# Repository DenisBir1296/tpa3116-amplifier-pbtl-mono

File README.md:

tpa3116 PBTL mono amplifier board

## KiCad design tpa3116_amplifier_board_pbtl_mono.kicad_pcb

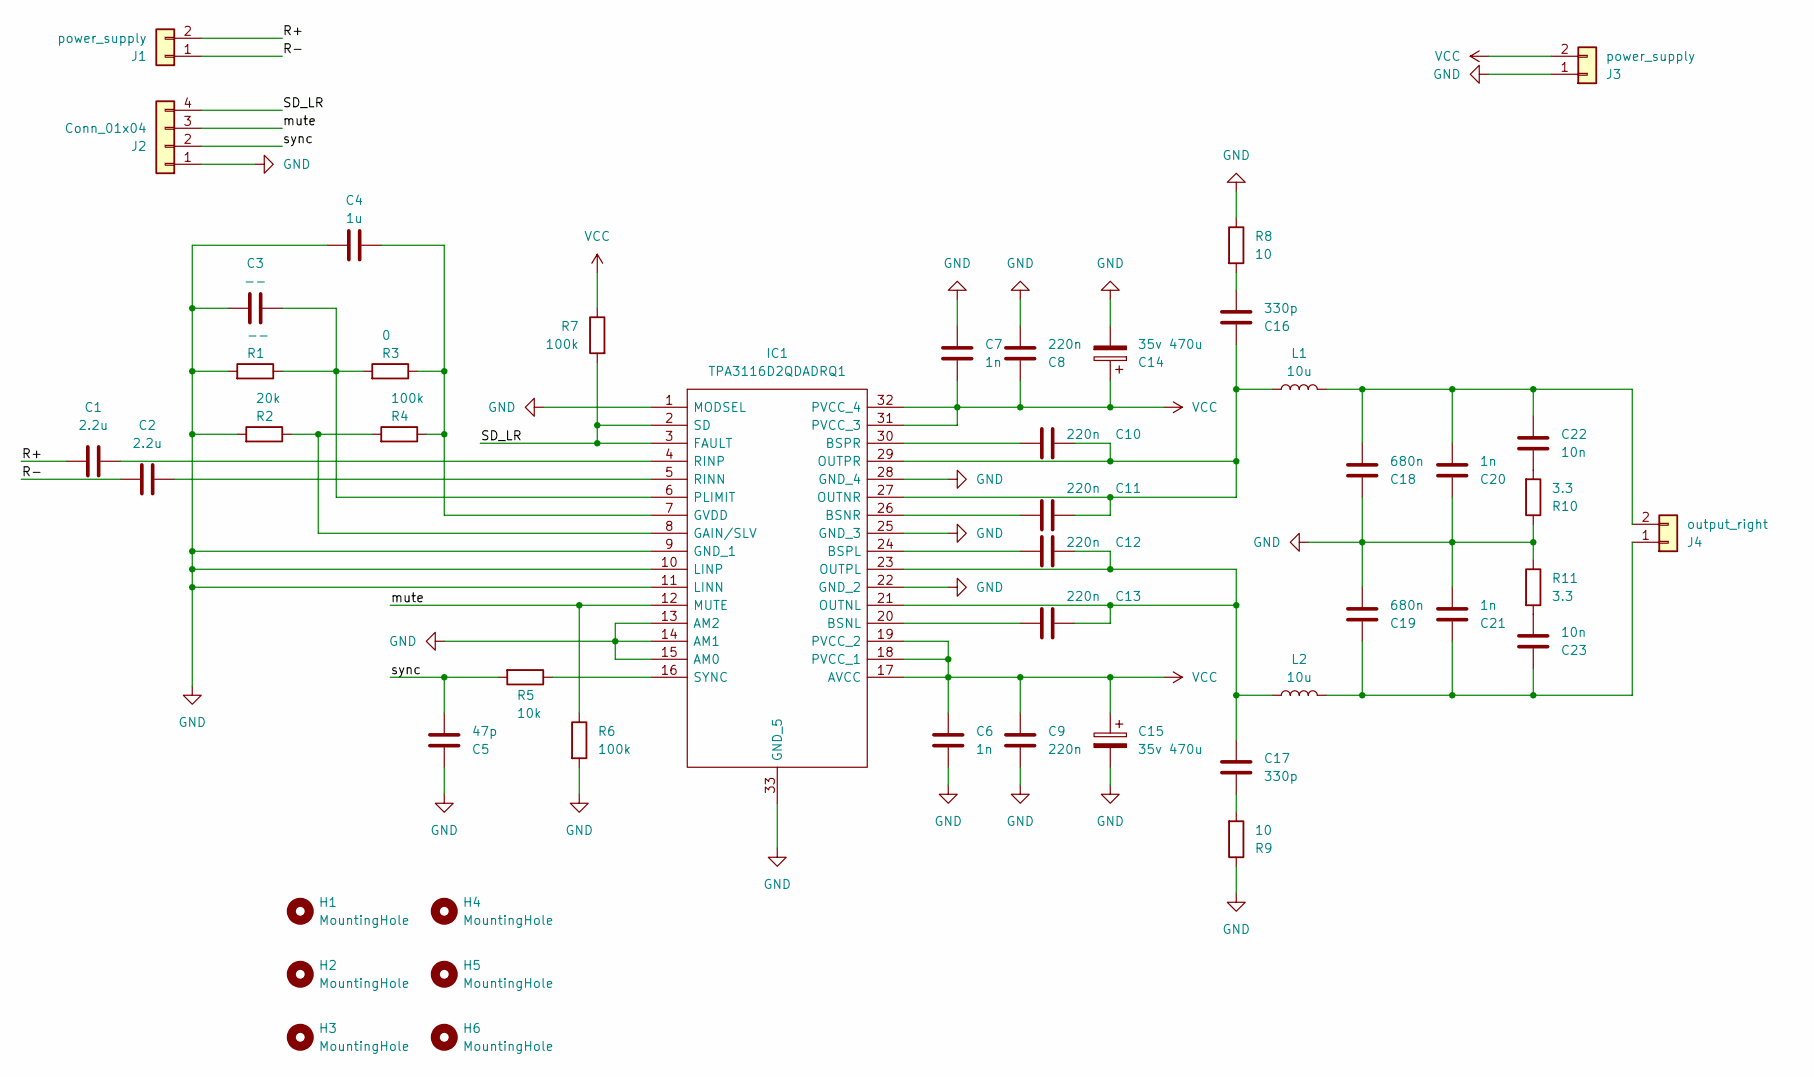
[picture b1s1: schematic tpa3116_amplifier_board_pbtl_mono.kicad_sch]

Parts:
C1, C2: 2.2u; C_0805_2012Metric
C3: --; C_0805_2012Metric
C4: 1u; C_0805_2012Metric
C5: 47p; C_0603_1608Metric
C6, C7, C20, C21: 1n; C_0603_1608Metric
C8, C9, C10, C11, C12, C13: 220n; C_0603_1608Metric
C14, C15: 35v 470u; CP_Radial_D10.0mm_P5.00mm
C16, C17: 330p; C_0603_1608Metric
C18, C19: 680n; C_1812_4532Metric
C22, C23: 10n; C_0603_1608Metric
H1, H2, H3, H4, H5, H6: MountingHole; MountingHole_3.2mm_M3_DIN965_Pad
IC1: TPA3116D2QDADRQ1; SOP65P810X120-33N; Manufacturer_Part_Number TPA3116D2QDADRQ1; Mouser Part Number 595-TPA3116D2QDADRQ1
J1: power_supply; JST_PH_B2B-PH-K_1x02_P2.00mm_Vertical
J2: Conn_01x04; JST_PH_B4B-PH-K_1x04_P2.00mm_Vertical
J3: power_supply; JST_VH_B2P-VH-B_1x02_P3.96mm_Vertical
J4: output_right; JST_VH_B2P-VH-B_1x02_P3.96mm_Vertical
L1, L2: 10u; L_12x12mm_H8mm
R1: --; R_0603_1608Metric
R2: 20k; R_0603_1608Metric
R3: 0; R_0603_1608Metric
R4, R6, R7: 100k; R_0603_1608Metric
R5: 10k; R_0603_1608Metric
R8, R9: 10; R_0805_2012Metric
R10, R11: 3.3; R_0603_1608Metric

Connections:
/R+: C1.1, J1.2
/R-: C2.1, J1.1
/SD_LR: IC1.2 (SD), IC1.3 (FAULT), J2.4, R7.2
/mute: IC1.12 (MUTE), J2.3, R6.1
/sync: C5.2, J2.2, R5.2
GND: C3.1, C4.1, C5.1, C6.2, C7.1, C8.2, C9.2, C14.2, C15.2, C18.1, C19.2, C20.1, C21.2, IC1.1 (MODSEL), IC1.9 (GND_1), IC1.10 (LINP), IC1.11 (LINN), IC1.13 (AM2), IC1.14 (AM1), IC1.15 (AM0), IC1.22 (GND_2), IC1.25 (GND_3), IC1.28 (GND_4), IC1.33 (GND_5), J2.1, J3.1, R1.2, R2.2, R6.2, R8.1, R9.1, R10.1, R11.1
unnamed: C16.2, R8.2
unnamed: C17.2, R9.2
unnamed: C22.2, R10.2
unnamed: C23.2, R11.2
unnamed: C13.2, IC1.20 (BSNL)
unnamed: C11.2, IC1.26 (BSNR)
unnamed: C12.2, IC1.24 (BSPL)
unnamed: C10.2, IC1.30 (BSPR)
unnamed: IC1.8 (GAIN/SLV), R2.1, R4.2
unnamed: C4.2, IC1.7 (GVDD), R3.1, R4.1
unnamed: C12.1, C13.1, C17.1, IC1.21 (OUTNL), IC1.23 (OUTPL), L2.1
unnamed: C10.1, C11.1, C16.1, IC1.27 (OUTNR), IC1.29 (OUTPR), L1.1
unnamed: C3.2, IC1.6 (PLIMIT), R1.1, R3.2
unnamed: C2.2, IC1.5 (RINN)
unnamed: C1.2, IC1.4 (RINP)
unnamed: IC1.16 (SYNC), R5.1
unnamed: C19.1, C21.1, C23.1, J4.1, L2.2
unnamed: C18.2, C20.2, C22.1, J4.2, L1.2
VCC: C6.1, C7.2, C8.1, C9.1, C14.1, C15.1, IC1.17 (AVCC), IC1.18 (PVCC_1), IC1.19 (PVCC_2), IC1.31 (PVCC_3), IC1.32 (PVCC_4), J3.2, R7.1

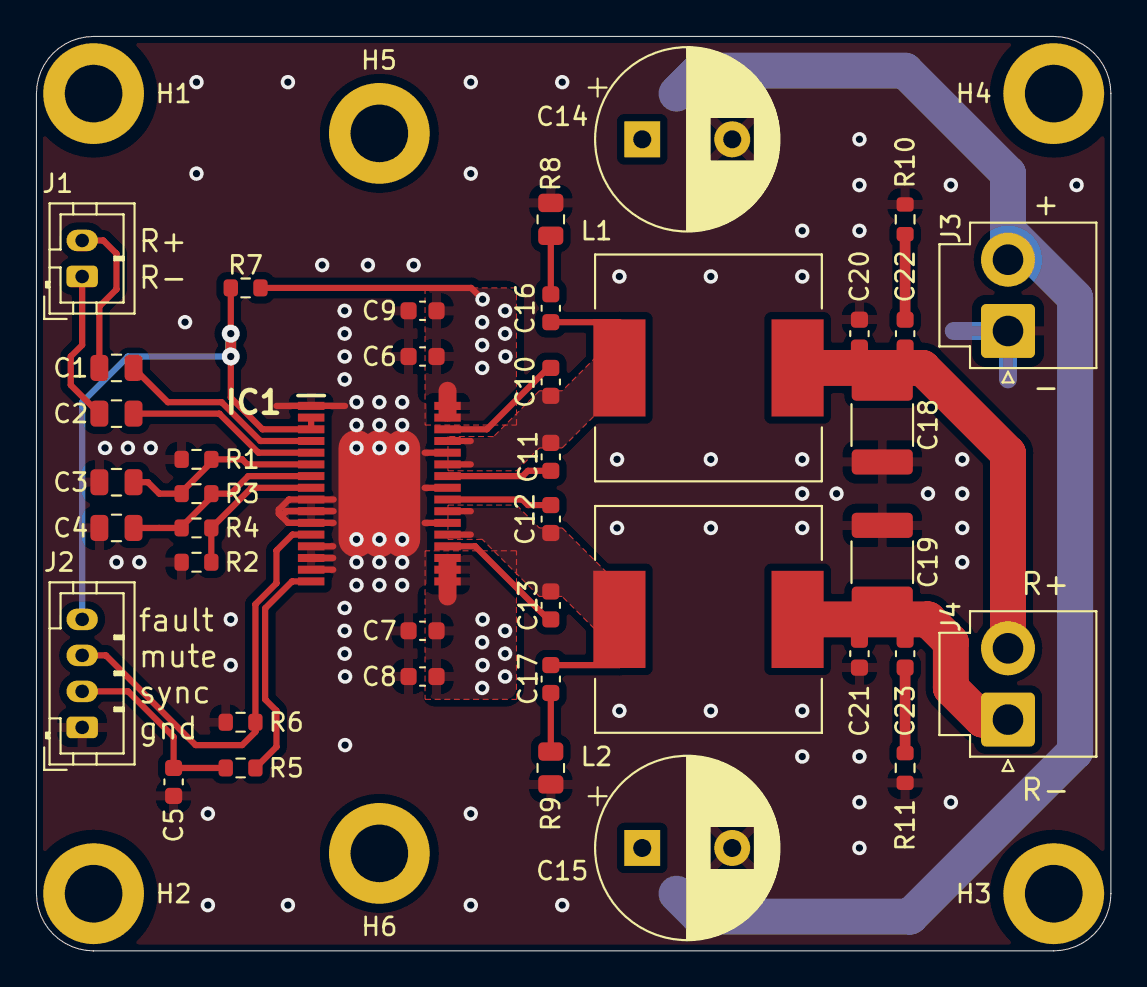
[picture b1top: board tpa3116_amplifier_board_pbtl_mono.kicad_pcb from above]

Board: 2 copper layers, 59.7 x 50.8 mm, 47 parts (0 on the bottom side), 25 nets.

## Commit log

2025-08-07 create
2025-08-07 Подправил дорожки и расположение R8, R9, отодвинул назад C14, C15
2025-08-07 заменил конденсаторы C1, С2 на smd
2025-08-07 изменил номинал конденсатора C3
2025-08-07 добавил изображение
2025-08-09 Перевернул входные разъемы, изменил номинал конденсаторов входных
2025-08-09 заменил входные разъемы на PH 2.0
2025-08-09 Изменил расположение переходных отверстий
2025-08-09 Увеличил размер отверстий под VH3.96
2025-08-12 Убрал лишние переходные отверстия, изображение обновил
2025-08-12 подправил readme
